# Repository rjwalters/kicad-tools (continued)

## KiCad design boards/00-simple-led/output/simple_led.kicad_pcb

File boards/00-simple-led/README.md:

# Simple LED (Hello World)

The smallest board in the repo: a 5 V power header, a current-limiting resistor,
and an LED. Three components, three nets. It exists to exercise the *entire*
kicad-tools pipeline — project → schematic → ERC → PCB → zones → route → DRC →
LVS → manufacturing bundle — at the smallest scale where every stage still has
something to do, and its end-to-end result is pinned in CI.

## Quick Start

```bash
# One-command build (recommended)
kct build boards/00-simple-led

# Or run specific steps
kct build boards/00-simple-led --step schematic
kct build boards/00-simple-led --step pcb
kct build boards/00-simple-led --step route
kct build boards/00-simple-led --step verify

# Preview what would happen, touching nothing
kct build boards/00-simple-led --dry-run
```

`kct build` discovers `generate_design.py` generically (see
`src/kicad_tools/cli/build_cmd.py`), so no board-specific registration is
needed. The default manufacturer profile is JLCPCB.

Verify the committed artifacts without rebuilding anything:

```bash
kct check boards/00-simple-led/output/simple_led_routed.kicad_pcb
# Overall:   PASSED   (DRC + ERC + LVS + Manifest)

kct net-status boards/00-simple-led/output/simple_led_routed.kicad_pcb
# Summary: 3 nets total — Complete: 3 (all pads connected)
```

## Circuit Overview

```
    +5V ──── J1.1 ────┬──────────── VCC   (pour)
                      │
                     [R1]
                     330R
                      │
                      ├──────────── LED_ANODE
                      │
                     (D1)  LED, Vf ≈ 2 V
                      │
    GND ──── J1.2 ────┴──────────── GND   (pour)
```

Three nets: **`VCC`**, **`LED_ANODE`**, **`GND`**. `VCC` and `GND` are pour
nets (copper zones); `LED_ANODE` is the single trace-routed signal net — which
is exactly why this board is the cheapest possible end-to-end pipeline test.

### Resistor sizing

```
R = (V_in − V_f) / I = (5 V − 2 V) / 10 mA = 300 Ω  →  330 Ω (nearest E24)
```

330 Ω delivers roughly **9 mA**, which is safe and clearly visible. The
rationale is recorded in `generate_design.py`'s module docstring and under
`decisions:` in `project.kct`.

## Components

| Reference | Description | Value | Footprint | Part | LCSC |
|-----------|-------------|-------|-----------|------|------|
| J1 | Power input header (VCC, GND) | — | `PinHeader_1x02_P2.54mm_Vertical` | ZX-PZ2.54-1-2PZZ | C7501260 |
| R1 | Current-limiting resistor | 330 Ω | `R_0805_2012Metric` | 0805W8F3300T5E | C17630 |
| D1 | Indicator LED | Vf ≈ 2 V | `LED_D5.0mm` | 333-2SURD/S530-A3 | C87271 |

The 5 mm through-hole LED plus the 0805 SMD resistor make this a deliberately
mixed THT/SMD board — see the `decisions:` block in `project.kct`.

## Design Specifications

| Parameter | Value |
|-----------|-------|
| Input Voltage | 5 V |
| LED Forward Voltage | ~2 V |
| Target LED Current | 10 mA (≈9 mA actual with 330 Ω) |
| Board Size | 25 mm × 20 mm |
| Layers | 2 |
| Nets | 3 (`VCC`, `LED_ANODE`, `GND`) |
| Target Fab | JLCPCB |

## Files

| File | Description |
|------|-------------|
| `generate_design.py` | The recipe: builds project, schematic, PCB, routes, runs ERC/DRC/LVS, exports the manufacturing bundle. Accepts an optional output directory as `argv[1]`. |
| `project.kct` | Project specification — intent, requirements, component list, BOM/LCSC mapping, and the `decisions:` log. |
| `output/simple_led.kicad_sch` | Generated schematic |
| `output/simple_led.kicad_pcb` | Generated unrouted PCB (+ `.kicad_pro`, `.kicad_prl`) |
| `output/simple_led_routed.kicad_pcb` | Routed PCB (+ `.kicad_pro`, `.kicad_prl`, `.kicad_dru` design rules) |
| `output/lvs.json` | Copper + label LVS report; `clean: true` on the committed board |
| `package_release.py` | Rebuilds the shipped package below through `kct readiness --generate`; run it after `generate_design.py` changes the PCB. |
| `output/manufacturing/` | Full fab bundle — see below |
| `output/readiness.json`, `output/readiness/` | Hash-bound readiness verdict and its gate evidence |

The `output/manufacturing/` bundle contains `gerbers/gerbers.zip`,
`bom_jlcpcb.csv`, `cpl_jlcpcb.csv`, `kicad_project.zip`, `manifest.json`,
`README.txt`, `report.md`, `report.pdf`, `schematic.pdf`,
`assembly-front.pdf`/`assembly-back.pdf`, the sign-off evidence
`check-report.json` and `native-drc.json`, the supplier review
`procurement-review.md`, and `images/` (front/back/copper/assembly renders
plus per-layer PNGs and the schematic render). `output/manufacturing.zip`
archives the whole bundle.

`output/board.json` is **not** committed — it is the public data contract
emitted on demand by `kct board-metrics`, which CI runs against a temporary
regeneration (below).

## Regenerating: always target a scratch directory

```bash
uv run python boards/00-simple-led/generate_design.py /tmp/board00
```

**Do not regenerate into the committed `output/` tree.** `generate_design.py`
falls back to `<board_dir>/output` when no `argv[1]` is given, which rewrites
tracked artifacts; `tests/conftest.py` additionally fails the test suite if
tracked files under `boards/**/output/` are modified during a test run. Passing
an explicit scratch directory is exactly what CI does, and it keeps a
verification run out of your diff.

If you *intend* to refresh the committed artifacts, do it as a deliberate,
reviewed change — not as a side effect of checking that the recipe still works.

## CI gate: `Board 00 End-to-End`

The `Board 00 End-to-End` job in `.github/workflows/ci.yml` runs on pushes to
`main` and on pull requests targeting `main`, inside a `kicad/kicad:10.0`
container. It is the contract this board must keep:

1. `uv sync --frozen --extra dev --python 3.12`, then `uv run kct build-native`
   — `uv sync` does not build the C++ router extension, and without it routing
   falls back to slow pure Python.
2. Regenerate into a clean temp directory:
   `uv run python boards/00-simple-led/generate_design.py /tmp/board00-ci`.
   The committed `output/` tree is never touched.
3. `uv run kct check /tmp/board00-ci/simple_led_routed.kicad_pcb` must print
   `Overall: PASSED` — a grep on `^Overall:[[:space:]]+PASSED` gates the build,
   so DRC **and** ERC **and** LVS **and** Manifest must all pass. No
   `--allow-incomplete`.
4. Mirror the regen into a `<board_dir>/output/` shape and emit `board.json`
   with `uv run kct board-metrics /tmp/board00-staging/00-simple-led`.
5. `scripts/ci/check_net_status.py` asserts plane-net completion — the raw
   `total_unconnected_pads` count, so a floating `VCC`/`GND` pad cannot hide
   behind the advisory power/plane classification (#4531).
6. `scripts/ci/check_board_00_e2e.py` asserts the artifact contract: every
   expected artifact present (schematic, PCB, routed PCB, `lvs.json`,
   `manufacturing/manifest.json`), `lvs.json` `clean: true`, and `board.json`
   reporting `status: ok`, `drc_violations: 0`, `lvs_clean: true`.

Note that the gate re-derives DRC from scratch; no `drc_report.json` is
committed (the old unproduced snapshots were removed in issue #7190, and
export preflight no longer trusts a report that is not bound to the PCB's
content). The recipe's own fast-fail gates (partial-route
detection, `write_lvs_report(require_clean=True)`) run inside step 2. Whether
this job is a *required* status check on `main` is a separate repo-admin
setting — it landed advisory, per the note in the job's own comment block.

## Why This Board?

It is the minimum viable proof that the toolchain works end to end. One signal
net means routing can never be the interesting failure — so when this job goes
red, the break is in the pipeline (schematic emission, zone creation, LVS,
export, manifest freshness), not in the router. That makes it the fastest
possible canary and the right place to start reading if you are new to the
repo.

## Related

- [`../README.md`](../README.md) — the board index and status table
- [01-voltage-divider](../01-voltage-divider/) — next step up: 4 components, a divider, and the same pipeline
- [02-charlieplex-led](../02-charlieplex-led/) — where routing starts to be the hard part

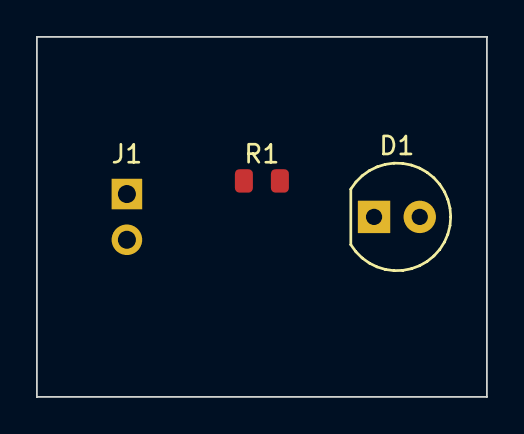
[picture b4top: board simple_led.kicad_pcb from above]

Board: 2 copper layers, 25.0 x 20.0 mm, 3 parts (0 on the bottom side), 3 nets, no tracks yet.

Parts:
D1: LED; LED_D5.0mm
J1: PWR; PinHeader_1x02_P2.54mm_Vertical
R1: 330; R_0805_2012Metric

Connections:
GND: D1.1 (K), J1.2
LED_ANODE: D1.2 (A), R1.2
VCC: J1.1, R1.1

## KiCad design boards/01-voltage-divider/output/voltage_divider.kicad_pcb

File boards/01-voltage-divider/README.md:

# Voltage Divider Demo

This demo demonstrates the complete kicad-tools workflow by creating the simplest possible PCB: a 4-component voltage divider.

## Quick Start

```bash
# One-command build (recommended)
kct build boards/01-voltage-divider

# Or run specific steps
kct build boards/01-voltage-divider --step schematic
kct build boards/01-voltage-divider --step pcb
kct build boards/01-voltage-divider --step route
kct build boards/01-voltage-divider --step verify

# Preview what would happen
kct build boards/01-voltage-divider --dry-run
```

## Circuit Overview

```
    +5V ─────┬─────────── J1 (Input)
             │
            [R1]
            10k
             │
    VOUT ────┼─────────── J2 (Output)
             │
            [R2]
            10k
             │
    GND ─────┴─────────── (Common)
```

Two 10k resistors divide the 5V input to produce 2.5V output (50% division ratio).

## Components

| Reference | Description | Footprint |
|-----------|-------------|-----------|
| J1 | Input connector (5V, GND) | 2.54mm pin header |
| J2 | Output connector (VOUT, GND) | 2.54mm pin header |
| R1 | Voltage divider (top) | 0805 SMD 10k |
| R2 | Voltage divider (bottom) | 0805 SMD 10k |

## Files

| File | Description |
|------|-------------|
| `generate_design.py` | Script to generate schematic, PCB, and route |
| `project.kct` | Project specification with requirements |
| `output/voltage_divider.kicad_sch` | Generated schematic |
| `output/voltage_divider.kicad_pcb` | Generated unrouted PCB |
| `output/voltage_divider_routed.kicad_pcb` | Routed PCB |

## Advanced: Manual Build

For more control, run the Python script directly. See [Prerequisites](../README.md#prerequisites-for-manual-build) for environment setup.

### Step 1: Generate the Design

```bash
# From repository root
uv run python boards/01-voltage-divider/generate_design.py
```

This creates:
- Schematic with all components and nets
- PCB with components placed on 30mm x 25mm board
- Routed PCB with all traces complete

### Step 2: Verify Output (Optional)

```bash
# Check for DRC violations
kct check output/voltage_divider_routed.kicad_pcb --mfr jlcpcb

# Generate BOM
kct bom output/voltage_divider.kicad_sch --format csv
```

### Step 3: View in KiCad (Optional)

Open `output/voltage_divider_routed.kicad_pcb` in KiCad to visualize the design.

## Design Specifications

| Parameter | Value |
|-----------|-------|
| Input Voltage | 5V |
| Output Voltage | 2.5V |
| Division Ratio | 0.5 (50%) |
| Board Size | 30mm x 25mm |
| Layers | 2 |
| Target Fab | JLCPCB |

## Why This Board?

This is the **simplest possible validation project** for kicad-tools. It exercises:

1. **Schematic Generation** - Creating symbols, wires, and net labels
2. **PCB Creation** - Placing footprints and defining the board outline
3. **Autorouting** - Connecting all nets with copper traces
4. **DRC Checking** - Validating against manufacturer rules

If the voltage divider routes successfully, the core workflow is verified.

## Related

- [02-charlieplex-led](../02-charlieplex-led/) - More complex routing challenge
- [03-usb-joystick](../03-usb-joystick/) - Mixed-signal design
- [04-stm32-devboard](../04-stm32-devboard/) - Programmatic schematic generation

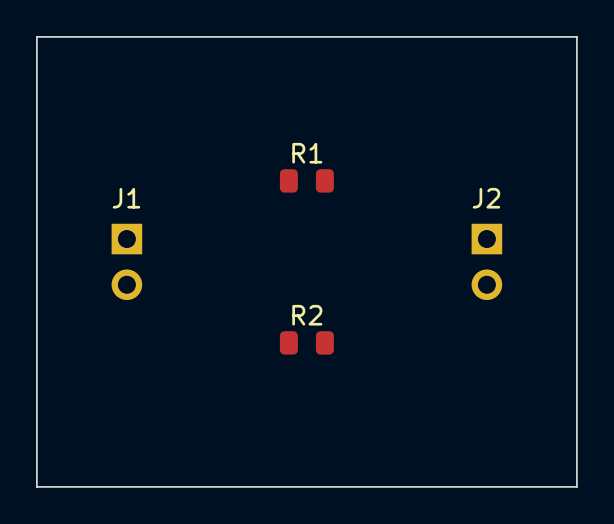
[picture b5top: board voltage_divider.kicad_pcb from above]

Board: 2 copper layers, 30.0 x 25.0 mm, 4 parts (0 on the bottom side), 3 nets, no tracks yet.

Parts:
J1: IN; PinHeader_1x02_P2.54mm_Vertical
J2: OUT; PinHeader_1x02_P2.54mm_Vertical
R1, R2: 10k; R_0805_2012Metric

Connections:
GND: J1.2, J2.2, R2.2
VIN: J1.1, R1.1
VOUT: J2.1, R1.2, R2.1

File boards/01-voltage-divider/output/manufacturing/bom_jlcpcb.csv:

Comment,Designator,Footprint,LCSC Part #
10k,"R1,R2",Resistor_SMD:R_0805_2012Metric,C17414
IN,J1,Connector_PinHeader_2.54mm:PinHeader_1x02_P2.54mm_Vertical,C7501260
OUT,J2,Connector_PinHeader_2.54mm:PinHeader_1x02_P2.54mm_Vertical,C7501260

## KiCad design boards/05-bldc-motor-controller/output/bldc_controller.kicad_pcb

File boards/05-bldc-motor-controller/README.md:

# Sensored BLDC Controller

Revision B is a real 42-component, 70 × 90 mm, four-layer small-motor controller:
ATmega328P-AU, DRV8313PWPR integrated triple half bridge, and TPS7A1650DGNR
5 V supply. It includes reverse-input protection, fuse, transient clamp,
charge-pump capacitors, current comparator, Hall inputs, AVR ISP, RUN switch
input, speed trimmer and working commutation firmware.

Start at 12 V with a 0.5 A current-limited bench supply, an unloaded motor,
RUN open and the speed input at its measured low-voltage end. The initial
phase-current target is 0.5 A; the nominal comparator trip is 1 A and firmware
caps duty at 25%. Physical motor operation and thermal performance have not
yet been measured. Read [HARDWARE.md](redesign/HARDWARE.md) before assembly,
programming or power-up; it contains all connector pinouts and verified BOM identities.

Generate the real circuit and reviewed route, run native refill/DRC/ERC and
manufacturer/LVS gates, and export its assembly bundle:

```sh
uv run python boards/05-bldc-motor-controller/design.py [output-directory]
```

Failed reconstruction leaves the preceding output intact. The route is explicit
reviewed copper in `redesign/routing.json`, guarded by a hash of the actual
component/pad/placement/net geometry. It combines automatic routing with manual
physical corrections; changing circuit geometry requires a new route and fresh
gates. No synthetic routing pads are present in the generated board.

The active revision-B recipe calls the generic physical power-stitch transaction
before its final native and manufacturing gates. It accepts existing complete
power copper or a safely completed candidate after real refill, preserving all
previous pad bonds and rejecting new native findings. Its retained `readiness/stitch`
ledger contains saved, refilled-before, proposed and refilled-candidate bytes,
native reports and physical pad components. Failed stage evidence is retained in
the `bldc-power-stitch-*` temporary directory named by the error.

Fresh reconstruction at main `7368bf597eaefb2dbe171f79db3c3216843a2ae6` already had
zero native opens/errors and clean copper LVS (149 bound pads); the historical
57-open legacy audit does not describe this active recipe. The generic split-plane
regression in `tests/fixtures/stitch-5388` demonstrates why added vias alone cannot
prove completion. Issue #4410 remains open for its later routing/Kelvin/QFN phases.

The manufacturing bundle has 36 SMT placements; hand-solder J1–J5 and RV1.
Solder both driver/regulator exposed pads. Use the included local symbol and
footprint libraries, native drawings, BOM/CPL and firmware. Fresh reconstruction
passed native KiCad DRC/ERC with zero findings and manufacturer checks with
zero errors or warnings. These fabrication checks do not replace motor and
thermal bench validation.

The original DRV8301 circuit is retained in [legacy_drv8301](legacy_drv8301/ARCHIVE.md)
as an electrically invalid historical regression fixture, documented in
[issue #4993](https://github.com/rjwalters/kicad-tools/issues/4993). Its generator
writes `regression-output`; the default command above builds revision B.

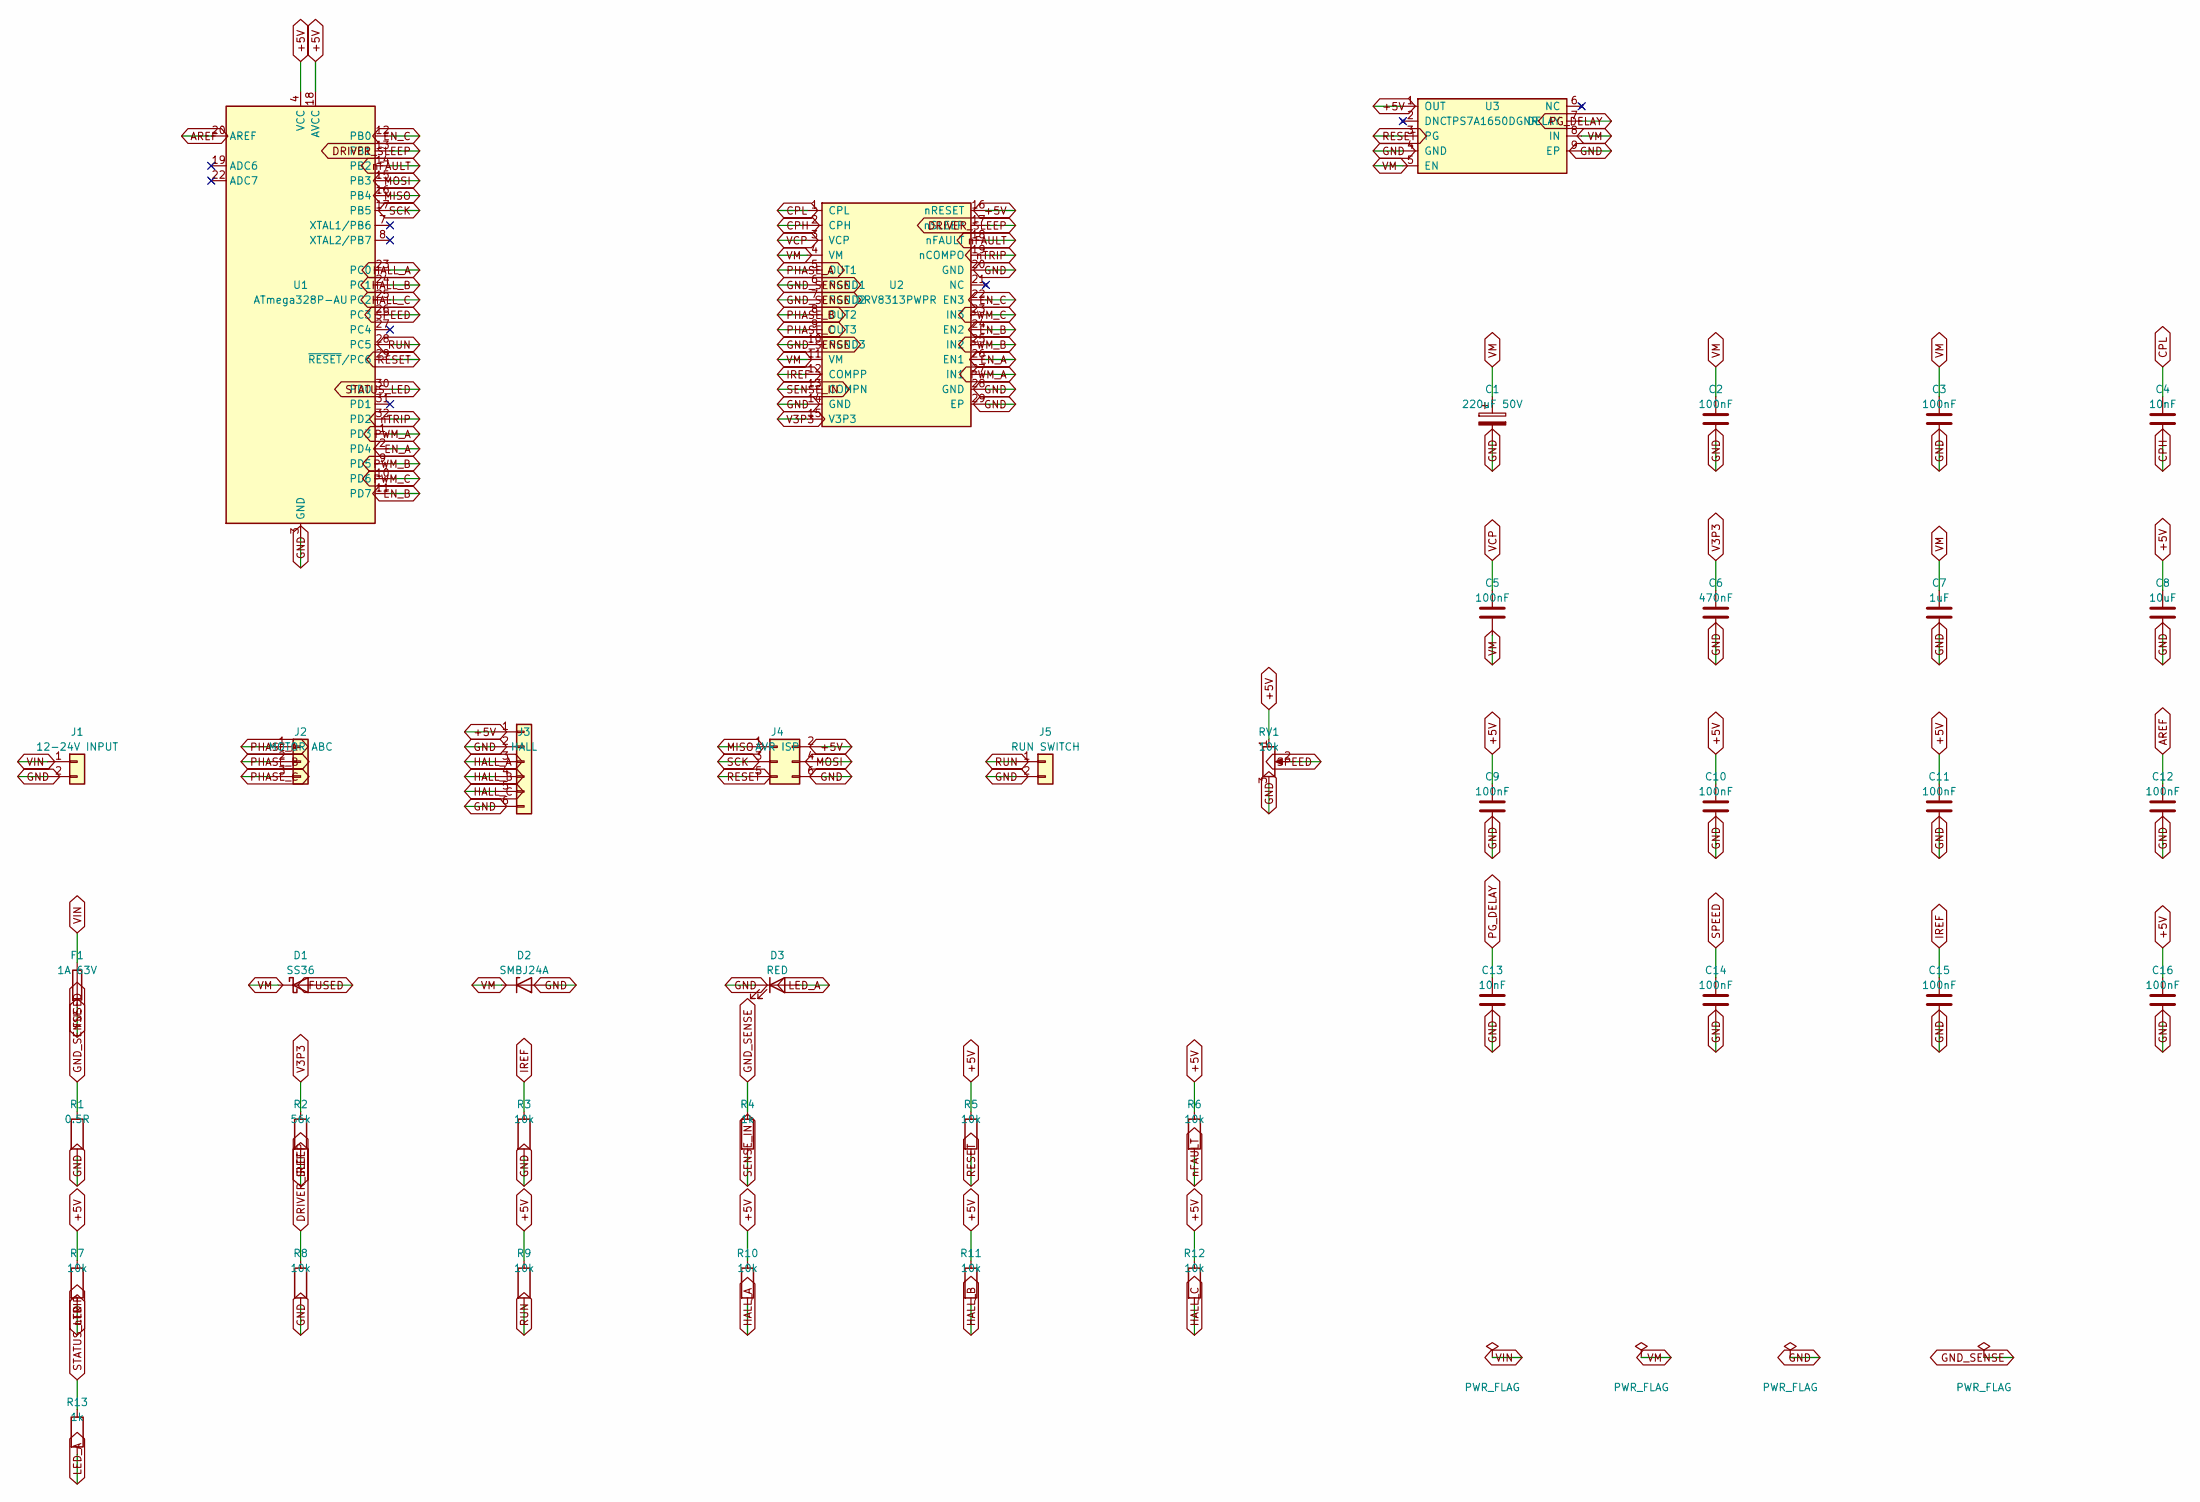
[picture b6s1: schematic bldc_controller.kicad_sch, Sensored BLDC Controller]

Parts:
C1: 220uF 50V; CP_Elec_8x10.5_PolarityMark; MPN EEEFT1H221AP; LCSC C178594
C2, C3, C5, C9, C10, C11, C12, C14, C15, C16: 100nF; C_0805_2012Metric; MPN CC0805KRX7R9BB104; LCSC C49678
C4, C13: 10nF; C_0805_2012Metric; MPN CL21B103KBANNNC; LCSC C1710
C6: 470nF; C_0805_2012Metric; MPN CL21B474KBFNNNE; LCSC C13967
C7: 1uF; C_0805_2012Metric; MPN CL21B105KBFNNNE; LCSC C28323
C8: 10uF; C_0805_2012Metric; MPN CL21A106KAYNNNE; LCSC C15850
D1: SS36; D_SMA; MPN SS36; LCSC C16015
D2: SMBJ24A; D_SMB; MPN SMBJ24A; LCSC C224017
D3: RED; LED_0805_2012Metric; MPN NCD0805R1; LCSC C84256
F1: 1A 63V; Fuse_1206_3216Metric; MPN SF-1206S100-2; LCSC C3167176
J1: 12-24V INPUT; PinHeader_1x02_P2.54mm_Vertical; MPN ZX-PZ2.54-1-2PZZ; LCSC C7501260
J2: MOTOR ABC; PinHeader_1x03_P2.54mm_Vertical; MPN 2.54-1*3P; LCSC C49257
J3: HALL; PinHeader_1x06_P2.54mm_Vertical; MPN 2.54-1*6P; LCSC C37208
J4: AVR ISP; PinHeader_2x03_P2.54mm_Vertical; MPN 2.54-2*3P; LCSC C65114
J5: RUN SWITCH; PinHeader_1x02_P2.54mm_Vertical; MPN ZX-PZ2.54-1-2PZZ; LCSC C7501260
R1: 0.5R; R_2512_6332Metric; MPN WSL2512R5000FEA; LCSC C511023
R2: 56k; R_0805_2012Metric; MPN 0805W8F5602T5E; LCSC C17756
R3, R5, R6, R7, R8, R9, R10, R11, R12: 10k; R_0805_2012Metric; MPN 0805W8F1002T5E; LCSC C17414
R4, R13: 1k; R_0805_2012Metric; MPN 0805W8F1001T5E; LCSC C17513
RV1: 10k; Potentiometer_Bourns_3296W_Vertical; MPN 3296W-1-103LF; LCSC C34846
U1: ATmega328P-AU; TQFP-32_7x7mm_P0.8mm; MPN ATMEGA328P-AU; LCSC C14877
U2: DRV8313PWPR; TI_PWP0028C_EP3.4x9.7_Mask3.1x5.18_ThermalVias; MPN DRV8313PWPR; LCSC C92482
U3: TPS7A1650DGNR; HVSSOP-8-1EP_3x3mm_P0.65mm_EP1.57x1.89mm_ThermalVias; MPN TPS7A1650DGNR; LCSC C468238

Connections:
+5V: C8.1, C9.1, C10.1, C11.1, C16.1, J3.1, J4.2, R5.1, R6.1, R7.1, R9.1, R10.1, R11.1, R12.1, RV1.1, U1.4 (VCC), U1.6 (VCC), U1.18 (AVCC), U2.16 (nRESET), U3.1 (OUT)
AREF: C12.1, U1.20 (AREF)
CPH: C4.2, U2.2 (CPH)
CPL: C4.1, U2.1 (CPL)
DRIVER_SLEEP: R8.1, U1.13 (PB1), U2.17 (nSLEEP)
EN_A: U1.2 (PD4), U2.26 (EN1)
EN_B: U1.11 (PD7), U2.24 (EN2)
EN_C: U1.12 (PB0), U2.22 (EN3)
FUSED: D1.2 (A), F1.2
HALL_A: J3.3, R10.2, U1.23 (PC0)
HALL_B: J3.4, R11.2, U1.24 (PC1)
HALL_C: J3.5, R12.2, U1.25 (PC2)
IREF: C15.1, R2.2, R3.1, U2.12 (COMPP)
LED_A: D3.2 (A), R13.2
MISO: J4.1, U1.16 (PB4)
MOSI: J4.4, U1.15 (PB3)
PG_DELAY: C13.1, U3.7 (DELAY)
PHASE_A: J2.1, U2.5 (OUT1)
PHASE_B: J2.2, U2.8 (OUT2)
PHASE_C: J2.3, U2.9 (OUT3)
PWM_A: U1.1 (PD3), U2.27 (IN1)
PWM_B: U1.9 (PD5), U2.25 (IN2)
PWM_C: U1.10 (PD6), U2.23 (IN3)
RESET: J4.5, R5.2, U1.29 (~RESET/PC6), U3.3 (PG)
RUN: J5.1, R9.2, U1.28 (PC5)
SCK: J4.3, U1.17 (PB5)
SENSE_IN: R4.2, U2.13 (COMPN)
SPEED: C14.1, RV1.2, U1.26 (PC3)
STATUS_LED: R13.1, U1.30 (PD0)
V3P3: C6.1, R2.1, U2.15 (V3P3)
VCP: C5.1, U2.3 (VCP)
nFAULT: R6.2, U1.14 (PB2), U2.18 (nFAULT)
nTRIP: R7.2, U1.32 (PD2), U2.19 (nCOMPO)

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
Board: 4 copper layers, 42 parts (0 on the bottom side), 37 nets, no tracks yet.

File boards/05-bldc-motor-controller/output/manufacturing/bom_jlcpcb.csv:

Comment,Designator,Footprint,LCSC Part #
0.5R,R1,Resistor_SMD:R_2512_6332Metric,C511023
100nF,"C10,C11,C12,C14,C15,C16,C2,C3,C5,C9",Capacitor_SMD:C_0805_2012Metric,C49678
10k,RV1,Potentiometer_THT:Potentiometer_Bourns_3296W_Vertical,C34846
10k,"R10,R11,R12,R3,R5,R6,R7,R8,R9",Resistor_SMD:R_0805_2012Metric,C17414
10nF,"C13,C4",Capacitor_SMD:C_0805_2012Metric,C1710
10uF,C8,Capacitor_SMD:C_0805_2012Metric,C15850
12-24V INPUT,J1,Connector_PinHeader_2.54mm:PinHeader_1x02_P2.54mm_Vertical,C7501260
1A 63V,F1,Fuse:Fuse_1206_3216Metric,C3167176
1k,"R13,R4",Resistor_SMD:R_0805_2012Metric,C17513
1uF,C7,Capacitor_SMD:C_0805_2012Metric,C28323
220uF 50V,C1,board05_revB:CP_Elec_8x10.5_PolarityMark,C178594
470nF,C6,Capacitor_SMD:C_0805_2012Metric,C13967
56k,R2,Resistor_SMD:R_0805_2012Metric,C17756
ATmega328P-AU,U1,Package_QFP:TQFP-32_7x7mm_P0.8mm,C14877
AVR ISP,J4,Connector_PinHeader_2.54mm:PinHeader_2x03_P2.54mm_Vertical,C65114
DRV8313PWPR,U2,board05_revB:TI_PWP0028C_EP3.4x9.7_Mask3.1x5.18_ThermalVias,C92482
HALL,J3,Connector_PinHeader_2.54mm:PinHeader_1x06_P2.54mm_Vertical,C37208
MOTOR ABC,J2,Connector_PinHeader_2.54mm:PinHeader_1x03_P2.54mm_Vertical,C49257
RED,D3,LED_SMD:LED_0805_2012Metric,C84256
RUN SWITCH,J5,Connector_PinHeader_2.54mm:PinHeader_1x02_P2.54mm_Vertical,C7501260
SMBJ24A,D2,Diode_SMD:D_SMB,C224017
SS36,D1,Diode_SMD:D_SMA,C16015
TPS7A1650DGNR,U3,Package_SO:HVSSOP-8-1EP_3x3mm_P0.65mm_EP1.57x1.89mm_ThermalVias,C468238

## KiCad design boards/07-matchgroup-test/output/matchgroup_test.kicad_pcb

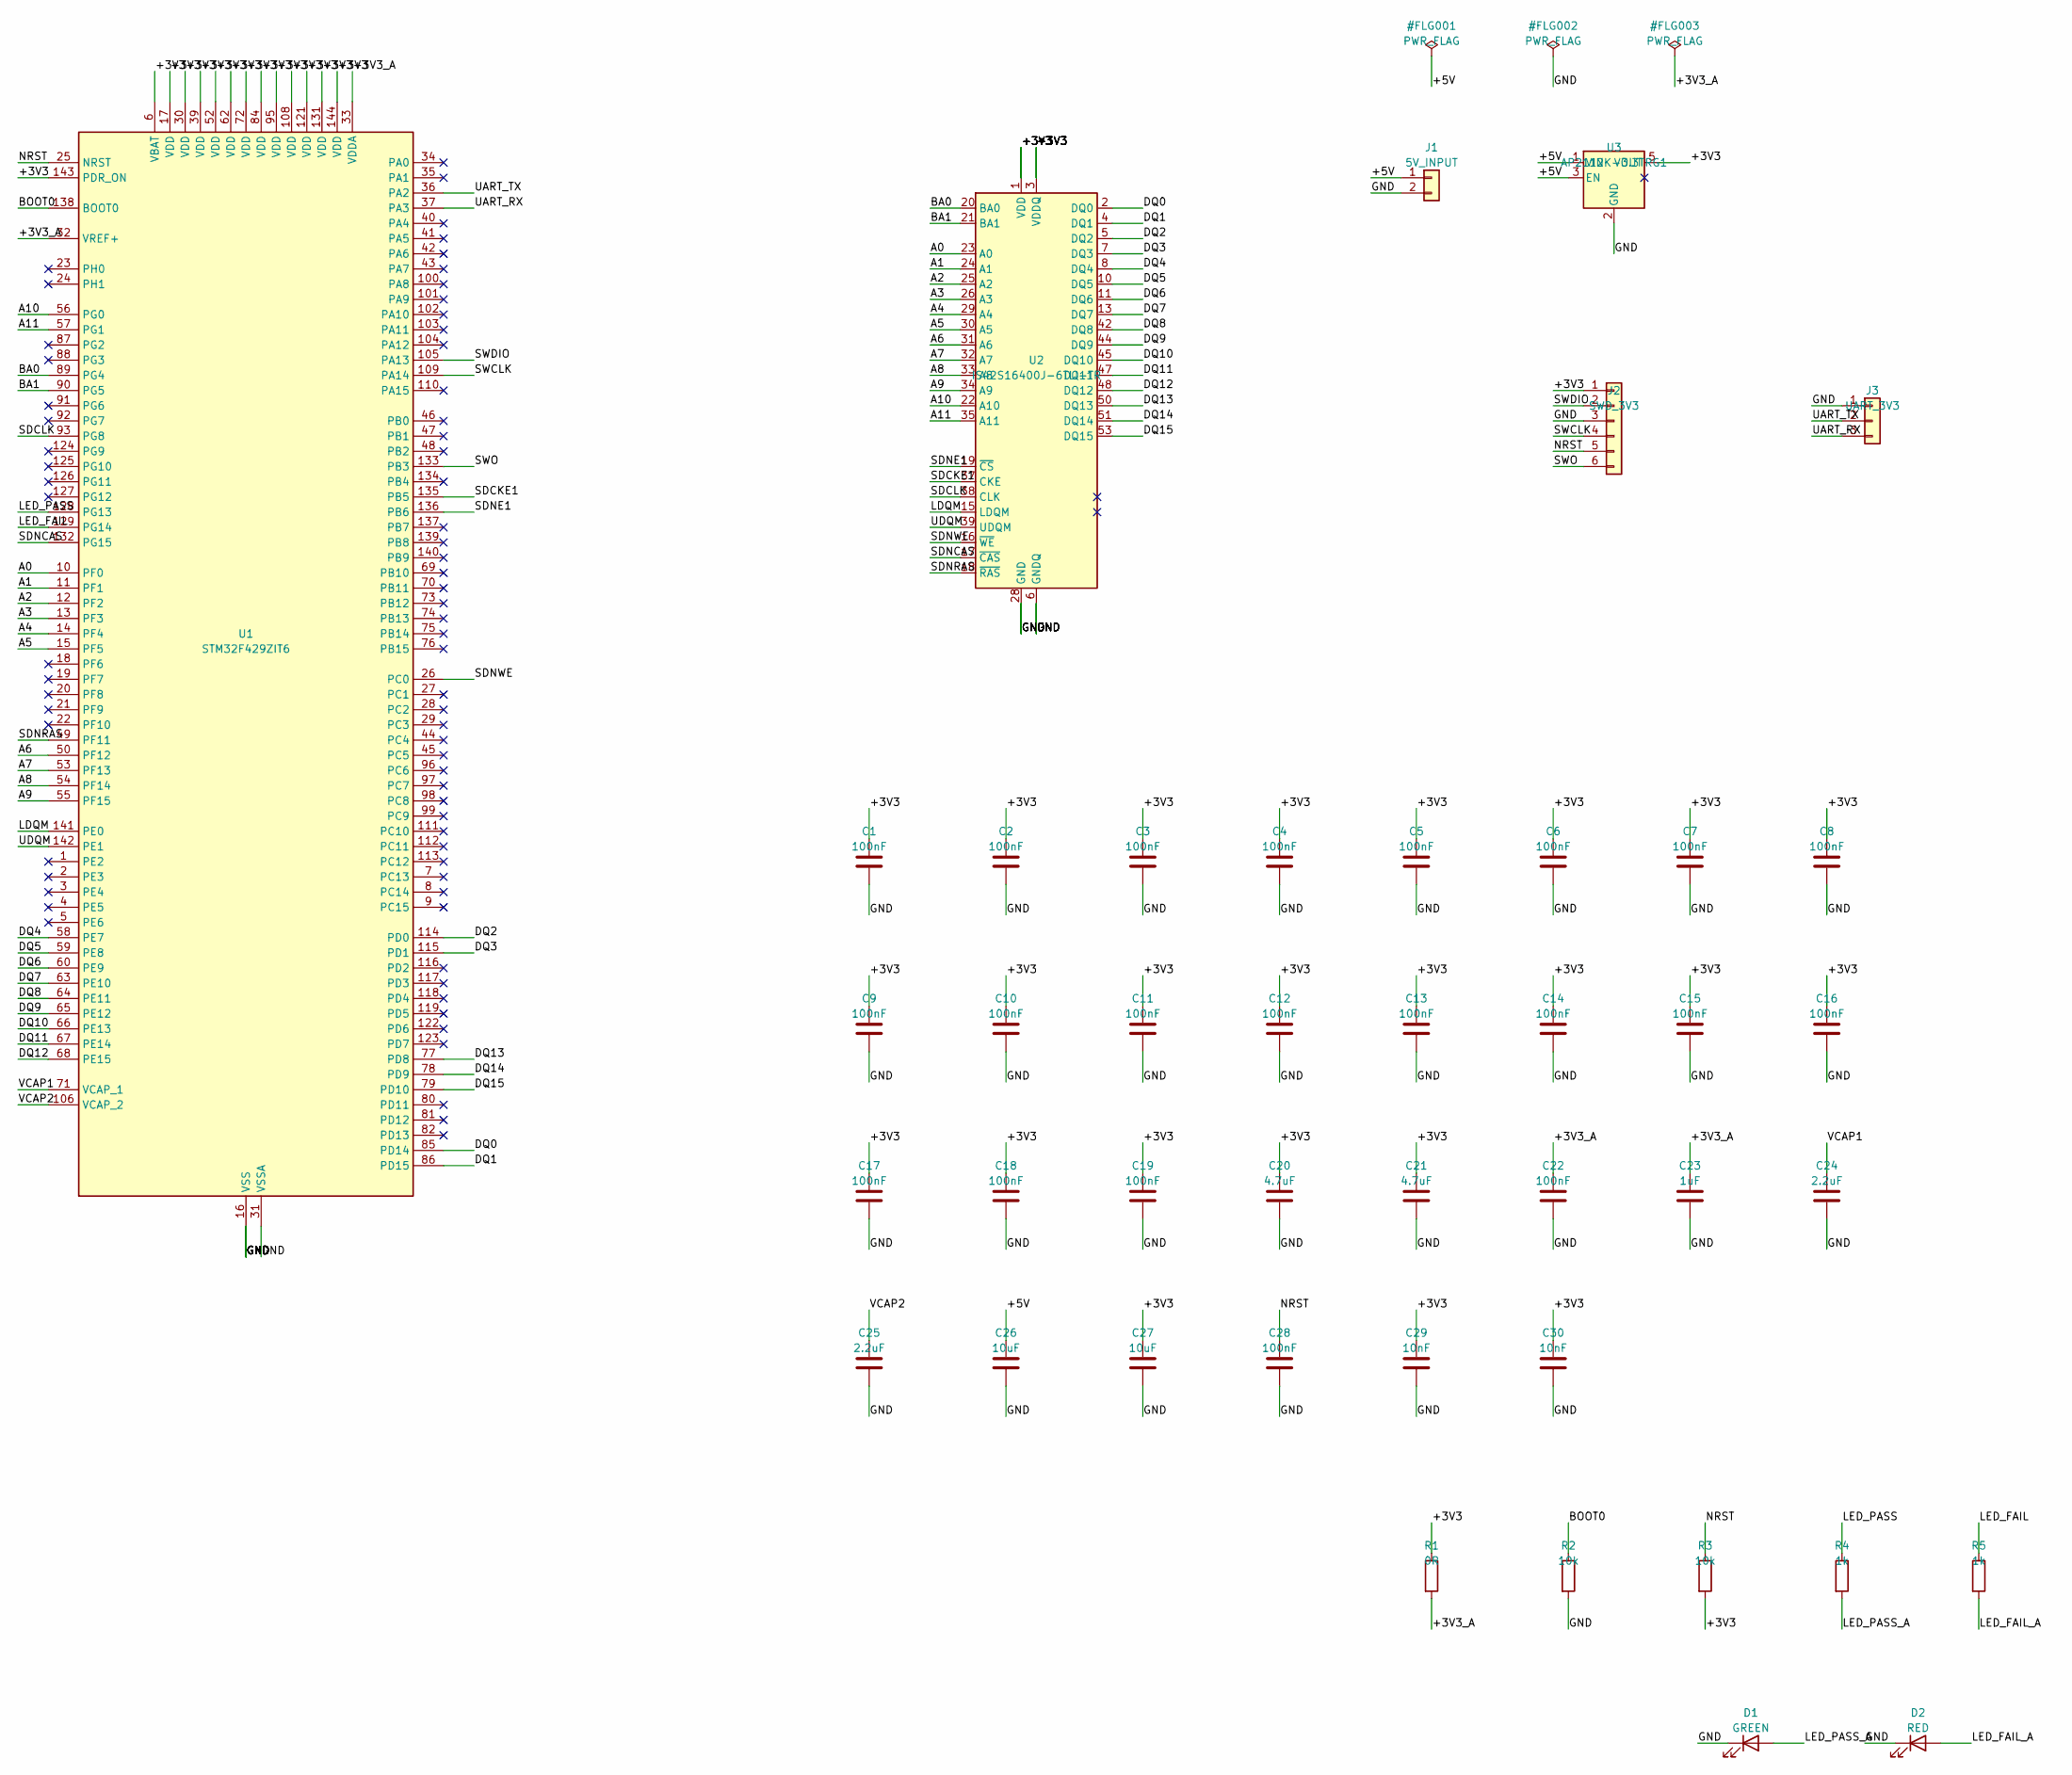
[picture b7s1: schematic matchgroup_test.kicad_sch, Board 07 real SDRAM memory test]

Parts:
C1, C2, C3, C4, C5, C6, C7, C8, C9, C10, C11, C12, C13, C14, C15, C16, C17, C18, C19, C22, C28: 100nF; C_0603_1608Metric; Manufacturer_Part_Number CC0603KRX7R9BB104; LCSC C14663
C20, C21: 4.7uF; C_0603_1608Metric; Manufacturer_Part_Number CL10A475KP8NNNC; LCSC C1705
C23: 1uF; C_0603_1608Metric; Manufacturer_Part_Number CL10A105KB8NNNC; LCSC C15849
C24, C25: 2.2uF; C_0603_1608Metric; Manufacturer_Part_Number CL10A225KO8NNNC; LCSC C23630
C26, C27: 10uF; C_0603_1608Metric; Manufacturer_Part_Number CL10A106KP8NNNC; LCSC C19702
C29, C30: 10nF; C_0603_1608Metric; Manufacturer_Part_Number CL10B103KB8NNNC; LCSC C1589
D1: GREEN; LED_0603_1608Metric; Manufacturer_Part_Number LTST-C190KGKT; LCSC C125094
D2: RED; LED_0603_1608Metric; Manufacturer_Part_Number LTST-C190KRKT; LCSC C94869
J1: 5V_INPUT; PinHeader_1x02_P2.54mm_Vertical; Manufacturer_Part_Number B-2100S02P-A110; LCSC C124375
J2: SWD_3V3; PinHeader_1x06_P2.54mm_Vertical; Manufacturer_Part_Number 2.54-1x6P; LCSC C37208
J3: UART_3V3; PinHeader_1x03_P2.54mm_Vertical; Manufacturer_Part_Number 2.54-1*3P; LCSC C49257
R1: 0R; R_0603_1608Metric; Manufacturer_Part_Number 0603WAF0000T5E; LCSC C21189
R2, R3: 10k; R_0603_1608Metric; Manufacturer_Part_Number 0603WAF1002T5E; LCSC C25804
R4, R5: 1k; R_0603_1608Metric; Manufacturer_Part_Number 0603WAF1001T5E; LCSC C21190
U1: STM32F429ZIT6; LQFP-144_20x20mm_P0.5mm; Manufacturer_Part_Number STM32F429ZIT6; LCSC C84808
U2: IS42S16400J-6TLI-TR; TSOP-II-54_22.2x10.16mm_P0.8mm; Manufacturer_Part_Number IS42S16400J-6TLI-TR; LCSC C17216754
U3: AP2112K-3.3TRG1; SOT-23-5; Manufacturer_Part_Number AP2112K-3.3TRG1; LCSC C51118

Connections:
+3V3: C1.1, C2.1, C3.1, C4.1, C5.1, C6.1, C7.1, C8.1, C9.1, C10.1, C11.1, C12.1, C13.1, C14.1, C15.1, C16.1, C17.1, C18.1, C19.1, C20.1, C21.1, C27.1, C29.1, C30.1, J2.1, R1.1, R3.2, U1.6 (VBAT), U1.17 (VDD), U1.30 (VDD), U1.39 (VDD), U1.52 (VDD), U1.62 (VDD), U1.72 (VDD), U1.84 (VDD), U1.95 (VDD), U1.108 (VDD), U1.121 (VDD), U1.131 (VDD), U1.143 (PDR_ON), U1.144 (VDD), U2.1 (VDD), U2.3 (VDDQ), U2.9 (VDDQ), U2.14 (VDD), U2.27 (VDD), U2.43 (VDDQ), U2.49 (VDDQ), U3.5 (VOUT)
+3V3_A: C22.1, C23.1, R1.2, U1.32 (VREF+), U1.33 (VDDA)
+5V: C26.1, J1.1, U3.1 (VIN), U3.3 (EN)
A0: U1.10 (PF0), U2.23 (A0)
A1: U1.11 (PF1), U2.24 (A1)
A2: U1.12 (PF2), U2.25 (A2)
A3: U1.13 (PF3), U2.26 (A3)
A4: U1.14 (PF4), U2.29 (A4)
A5: U1.15 (PF5), U2.30 (A5)
A6: U1.50 (PF12), U2.31 (A6)
A7: U1.53 (PF13), U2.32 (A7)
A8: U1.54 (PF14), U2.33 (A8)
A9: U1.55 (PF15), U2.34 (A9)
A10: U1.56 (PG0), U2.22 (A10)
A11: U1.57 (PG1), U2.35 (A11)
BA0: U1.89 (PG4), U2.20 (BA0)
BA1: U1.90 (PG5), U2.21 (BA1)
BOOT0: R2.1, U1.138 (BOOT0)
DQ0: U1.85 (PD14), U2.2 (DQ0)
DQ1: U1.86 (PD15), U2.4 (DQ1)
DQ2: U1.114 (PD0), U2.5 (DQ2)
DQ3: U1.115 (PD1), U2.7 (DQ3)
DQ4: U1.58 (PE7), U2.8 (DQ4)
DQ5: U1.59 (PE8), U2.10 (DQ5)
DQ6: U1.60 (PE9), U2.11 (DQ6)
DQ7: U1.63 (PE10), U2.13 (DQ7)
DQ8: U1.64 (PE11), U2.42 (DQ8)
DQ9: U1.65 (PE12), U2.44 (DQ9)
DQ10: U1.66 (PE13), U2.45 (DQ10)
DQ11: U1.67 (PE14), U2.47 (DQ11)
DQ12: U1.68 (PE15), U2.48 (DQ12)
DQ13: U1.77 (PD8), U2.50 (DQ13)
DQ14: U1.78 (PD9), U2.51 (DQ14)
DQ15: U1.79 (PD10), U2.53 (DQ15)
GND: C1.2, C2.2, C3.2, C4.2, C5.2, C6.2, C7.2, C8.2, C9.2, C10.2, C11.2, C12.2, C13.2, C14.2, C15.2, C16.2, C17.2, C18.2, C19.2, C20.2, C21.2, C22.2, C23.2, C24.2, C25.2, C26.2, C27.2, C28.2, C29.2, C30.2, D1.1 (K), D2.1 (K), J1.2, J2.3, J3.1, R2.2, U1.16 (VSS), U1.31 (VSSA), U1.38 (VSS), U1.51 (VSS), U1.61 (VSS), U1.83 (VSS), U1.94 (VSS), U1.107 (VSS), U1.120 (VSS), U1.130 (VSS), U2.6 (GNDQ), U2.12 (GNDQ), U2.28 (GND), U2.41 (GND), U2.46 (GNDQ), U2.52 (GNDQ), U2.54 (GND), U3.2 (GND)
LDQM: U1.141 (PE0), U2.15 (LDQM)
LED_FAIL: R5.1, U1.129 (PG14)
LED_FAIL_A: D2.2 (A), R5.2
LED_PASS: R4.1, U1.128 (PG13)
LED_PASS_A: D1.2 (A), R4.2
NRST: C28.1, J2.5, R3.1, U1.25 (NRST)
SDCKE1: U1.135 (PB5), U2.37 (CKE)
SDCLK: U1.93 (PG8), U2.38 (CLK)
SDNCAS: U1.132 (PG15), U2.17 (~CAS)
SDNE1: U1.136 (PB6), U2.19 (~CS)
SDNRAS: U1.49 (PF11), U2.18 (~RAS)
SDNWE: U1.26 (PC0), U2.16 (~WE)
SWCLK: J2.4, U1.109 (PA14)
SWDIO: J2.2, U1.105 (PA13)
SWO: J2.6, U1.133 (PB3)
UART_RX: J3.3, U1.37 (PA3)
UART_TX: J3.2, U1.36 (PA2)
UDQM: U1.142 (PE1), U2.39 (UDQM)
VCAP1: C24.1, U1.71 (VCAP_1)
VCAP2: C25.1, U1.106 (VCAP_2)

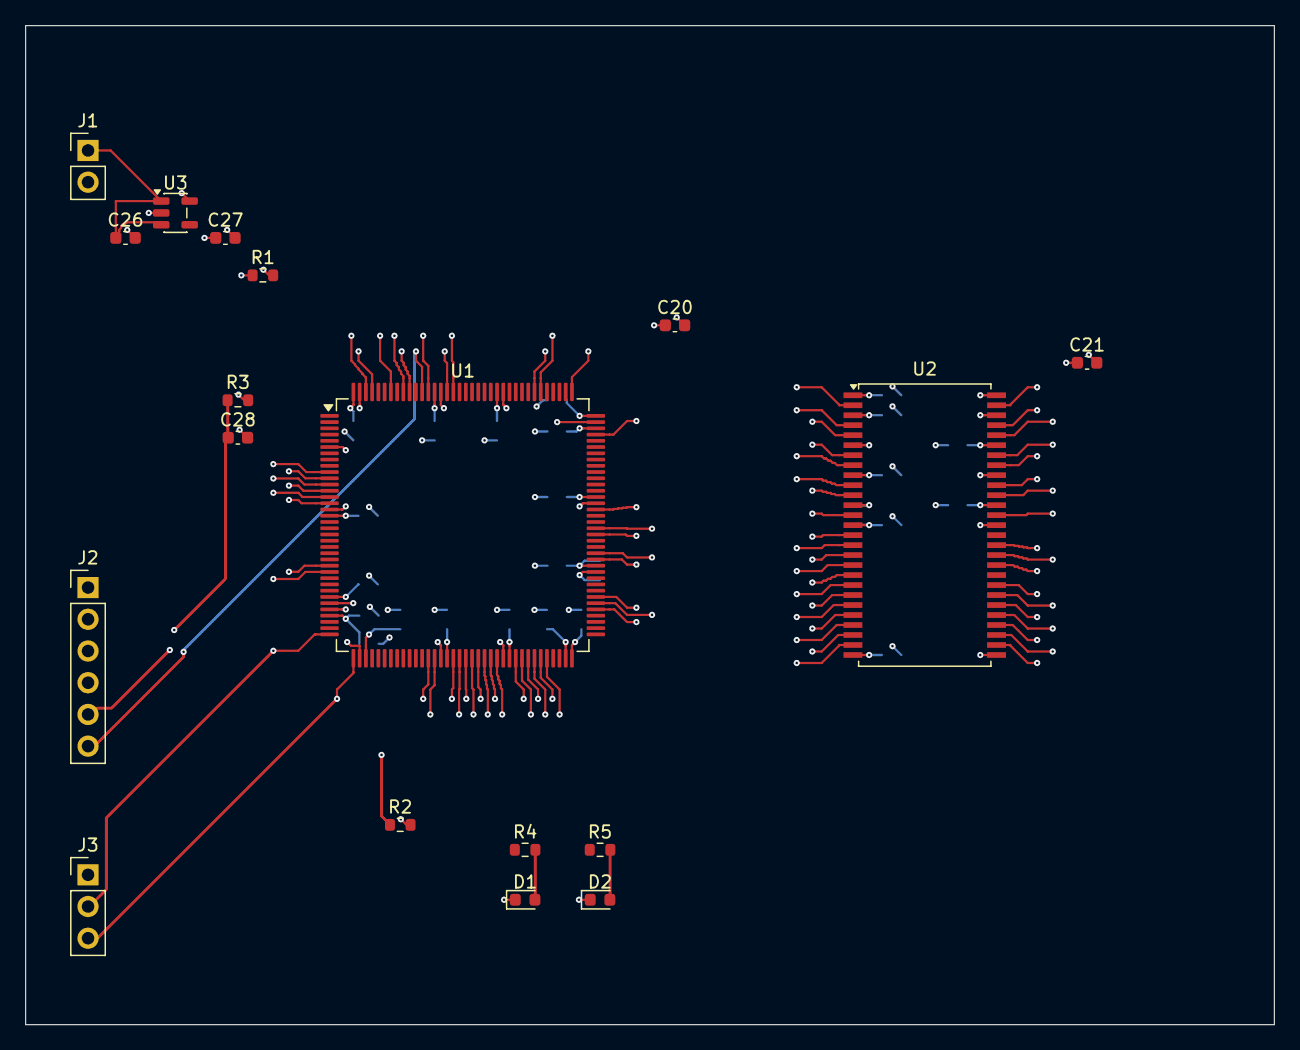
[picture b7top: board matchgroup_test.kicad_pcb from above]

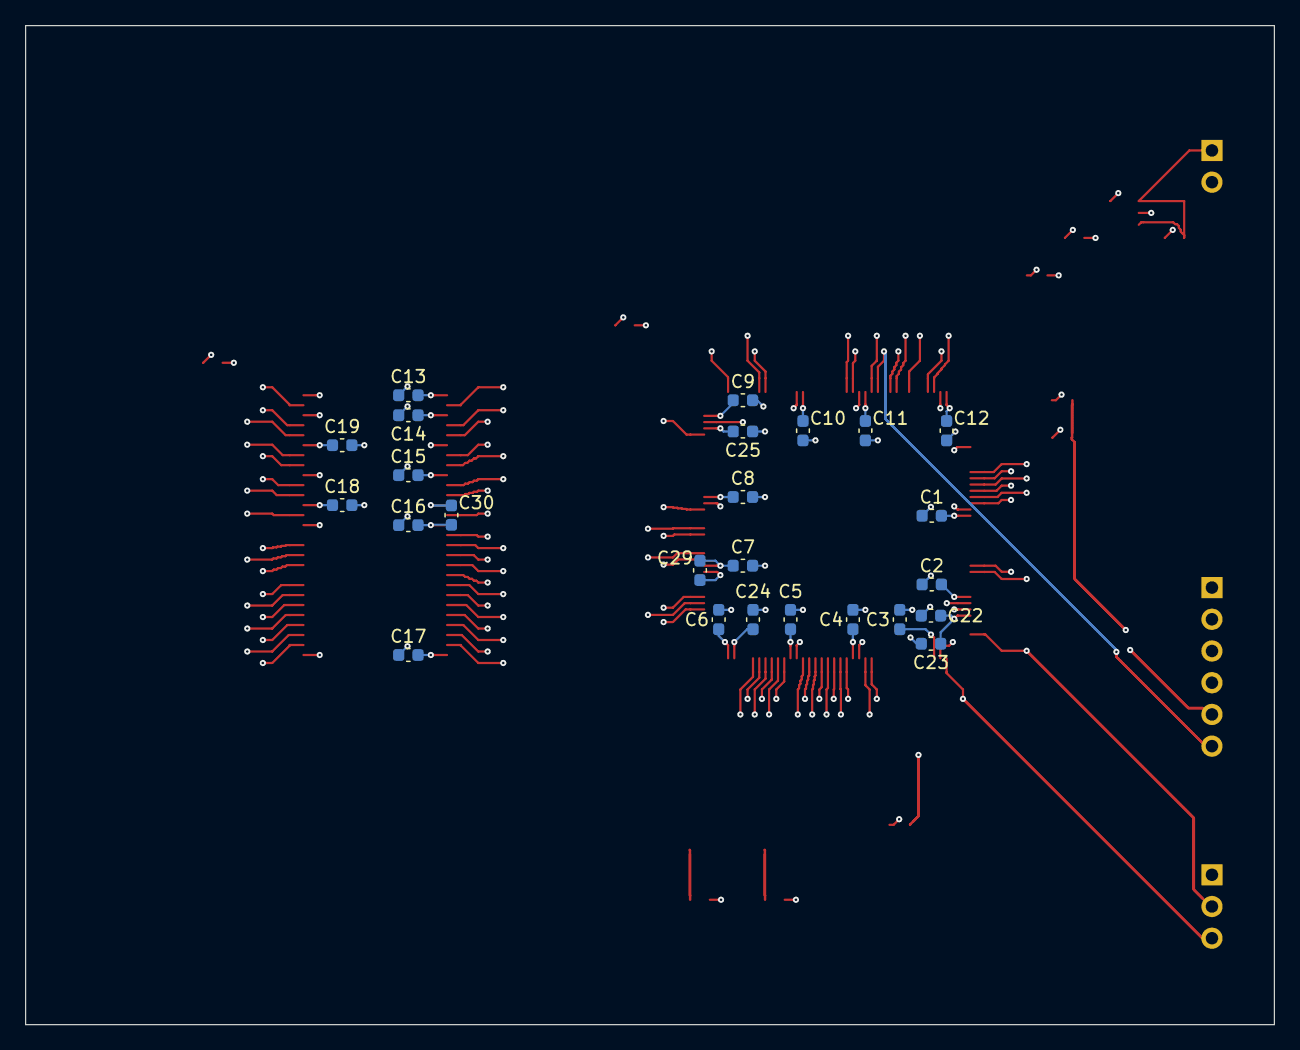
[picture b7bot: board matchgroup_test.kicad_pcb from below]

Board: 6 copper layers, 100.0 x 80.0 mm, 43 parts (25 on the bottom side), 55 nets.
